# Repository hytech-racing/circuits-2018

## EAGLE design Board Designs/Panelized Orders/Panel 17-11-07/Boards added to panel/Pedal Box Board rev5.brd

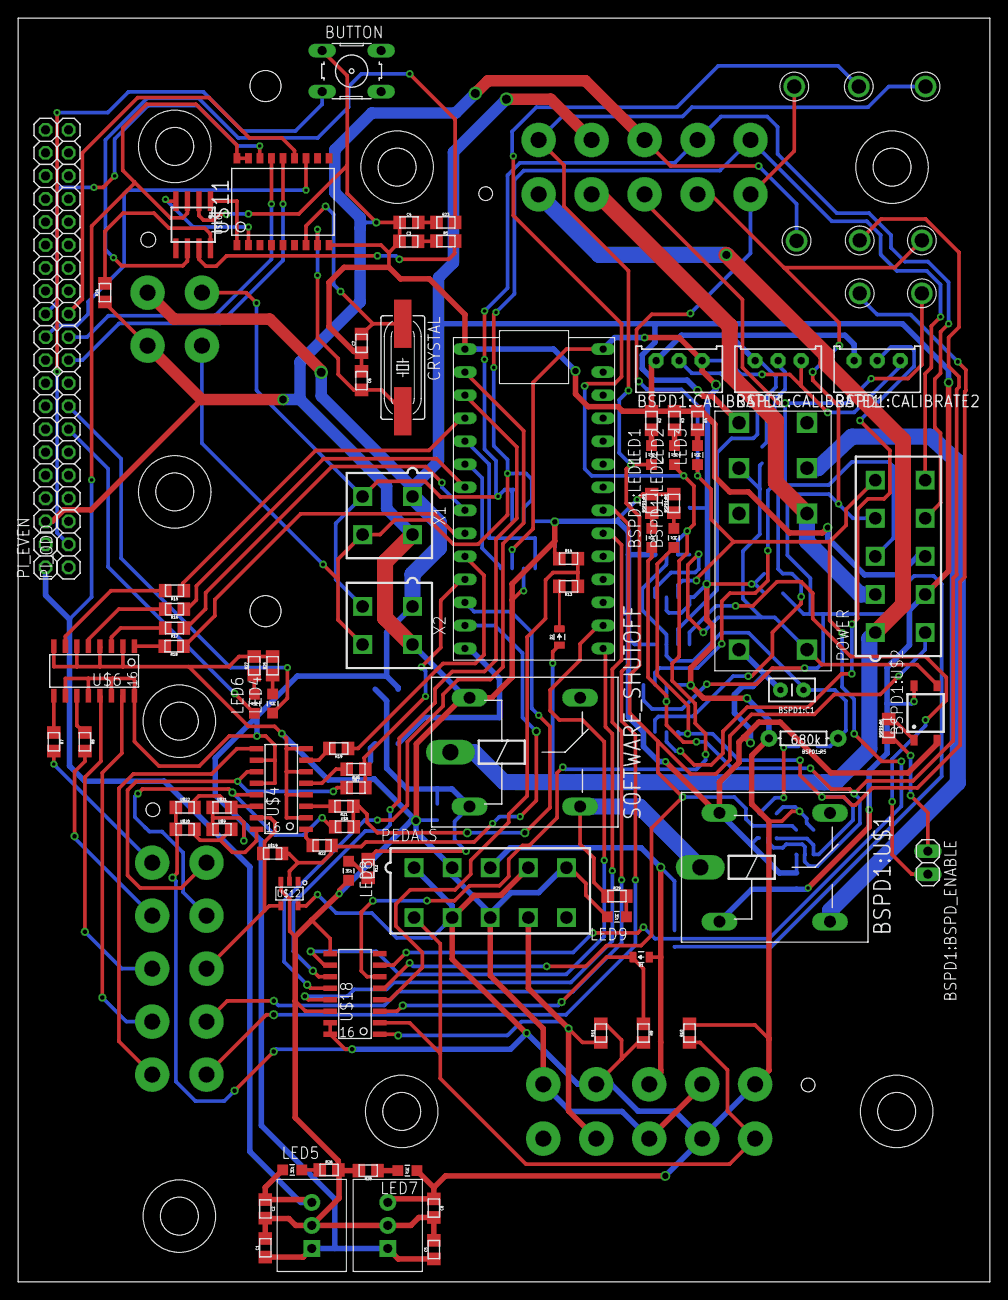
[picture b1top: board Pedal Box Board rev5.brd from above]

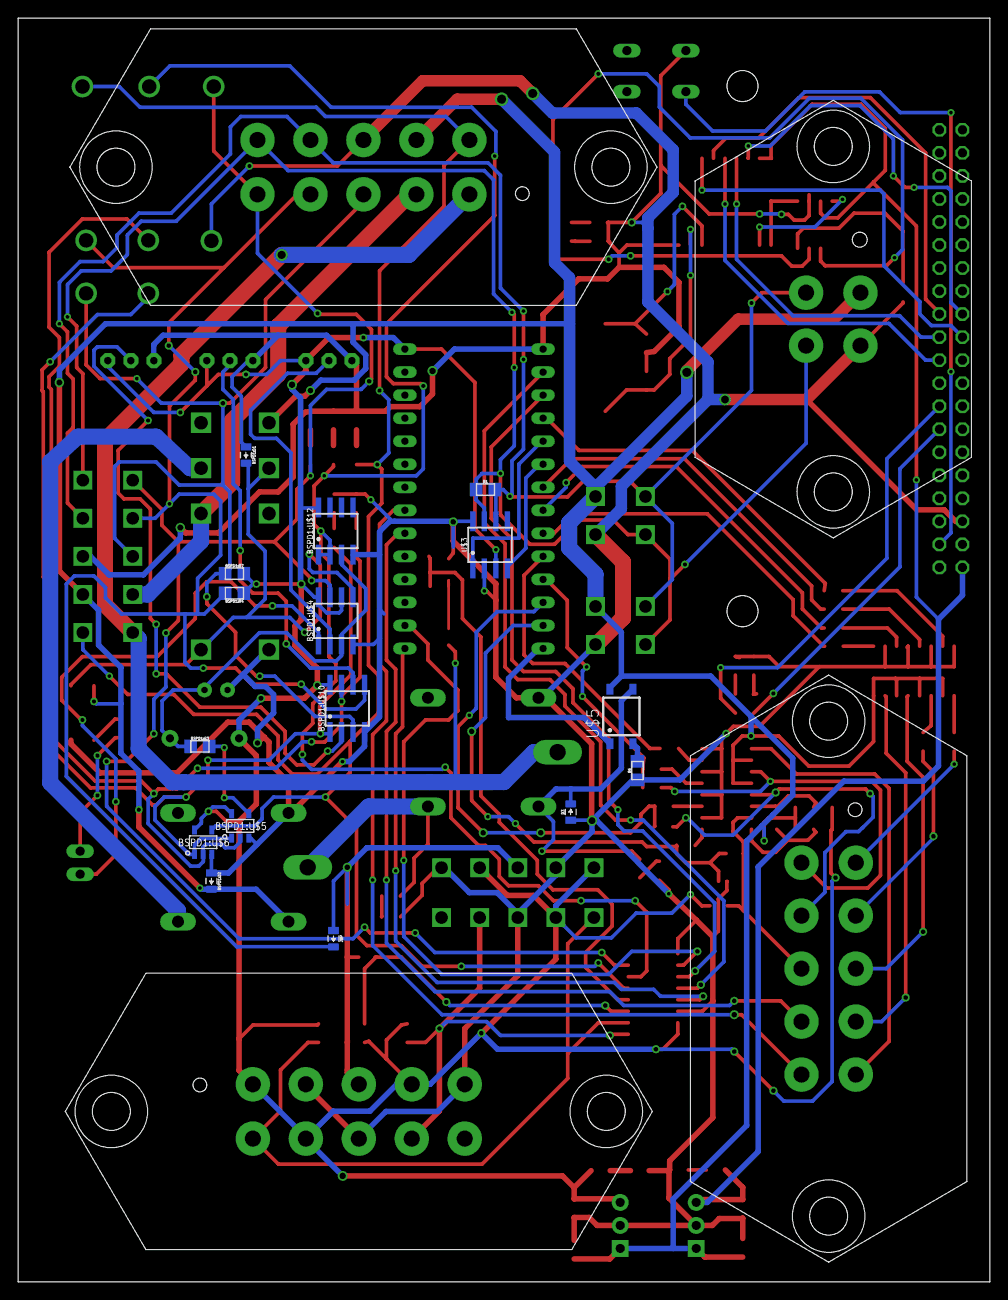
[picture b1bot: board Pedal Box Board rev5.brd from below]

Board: 2 copper layers, 107.2 x 139.4 mm, 113 parts (20 on the bottom side), 99 nets.

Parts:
BSPD1:BSPD_ENABLE: JUMPER; 1X02
BSPD1:C1: .47u; CAP-PTH-SMALLEZ
BSPD1:CALIBRATE1, BSPD1:CALIBRATE2, BSPD1:CALIBRATE3: TRIMPOT_3296
BSPD1:D1, BSPD1:D2: DIODE0805; 0805_D
BSPD1:LED1: RED; LED-805
BSPD1:LED2: YELLOW; LED-805
BSPD1:R3: 330; 0805
BSPD1:R4, BSPD1:R7: 10k; 0805
BSPD1:R5: 680k; AXIAL-0.3EZ
BSPD1:R6: 680; 0805
BSPD1:R8, BSPD1:R9: 270; 0805
BSPD1:U$1: G5LE; ZF112
BSPD1:U$2: CPC1002N; SOP04
BSPD1:U$3: JW2SN-DC12V; JW2SN
BSPD1:U$4, BSPD1:U$10: MCP6542SOIC; SOIC-08
BSPD1:U$5: SN74AHC1G09; SOT-23-5
BSPD1:U$6: SN74LVC1G08; SOT-23-5
BSPD1:U$11, BSPD1:U$13: TEST_POINT
BSPD1:U$12: MCP6002SOIC; SOIC-08
BUTTON: B3F-10XX
C1, C2, C5, C8: 10uF; 0805
C3, C4: 560pF; 0805
C6, C7: 22pF; 0805
CRYSTAL: 16MHz; HC49UP
D1, D2, D3: DIODE0805; 0805_D
IC2, IC3: TO-220
JMP: DIODE0805; 0805_D
LED1, LED6, LED8, LED9: RED; LED-805
LED2: YELLOW; LED-805
LED3, LED4: GREEN; LED-805
LED5, LED7: PURPLE; LED-805
PEDALS: MINIFIT_5566-10
PI_EVEN: 1X20
PI_ODD: 1X20
POWER: MINIFIT_5566-10
R1: 120; 0805
R2, R3, R15, R16, R17, R18, R19, R20, R21, R22, R27: 270; 0805
R4, R25, R26, R28: 200; 0805
R5, R23: 100; 0805
R6: 330; 0805
R7, R8: 0; 0805
R9, R10, R11: 10k; 0805
R12, R29: 1.2K; 0805
R13: 43k; 0805
R14: 12k; 0805
R24: 4.7k; 0805
SOFTWARE_SHUTOFF: G5LE; ZF112
U$1: TEENSY_3.2_SIMPLE
U$2, U$13, U$14, U$15, U$16, U$17: TEST_POINT
U$3, U$10: MCP2551; SOIC-08
U$4, U$6: TLP291-4; SOIC-16
U$5: CPC1002N; SOP04
U$7, U$8, U$9, U$19, U$20, U$21, U$22: JUMPER; 0805
U$11: MCP2515SMD; SOIC-18W
U$12: SN74LV1T34; SOT-23-5
U$18: MCP3208SOIC; SOIC-16
X1, X2: CONNECTOR-4; MINIFIT_5566-4
X3: CONNECTOR-4MX150L_VERTICAL-4; MX150L_VERTICAL-4
X4, X5, X6: CONNECTOR-10MX150L_VERTICAL-10; MX150L_VERTICAL-10

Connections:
+5V: BSPD1:CALIBRATE1.1, BSPD1:CALIBRATE2.1, BSPD1:CALIBRATE3.1, BSPD1:R4.1, BSPD1:R5.P$2, BSPD1:R7.2, BSPD1:U$4.6, BSPD1:U$4.8, BSPD1:U$5.5, BSPD1:U$6.5, BSPD1:U$10.8, BSPD1:U$12.8, C8.1, IC3.3, LED7.A, PEDALS.1, PEDALS.4, PEDALS.7, R9.2, R10.2, R11.2, U$1.VIN, U$3.3, U$12.5, U$18.15, U$18.16, U$20.1, U$22.1, X4.1, X4.4, X4.7
+5V/1: C2.1, IC2.3, LED5.A, PI_EVEN.1, U$10.3, U$11.17, U$11.18
+12V: BSPD1:D2.C, BSPD1:U$1.2, BSPD1:U$2.4, BSPD1:U$3.4, C1.1, C5.1, IC2.1, IC3.1, POWER.7, U$4.10, U$4.12, U$5.4, U$6.10, U$6.12, U$6.14, U$6.16, U$9.1, U$21.1, X1.1, X2.1, X3.1, X5.7
BSPD1:N$1: BSPD1:D1.C, BSPD1:U$2.3, BSPD1:U$3.3, BSPD1:U$3.COIL-, BSPD1:U$4.5
BSPD1:N$2: BSPD1:R3.2, BSPD1:U$5.4
BSPD1:N$3: BSPD1:R6.2, BSPD1:U$2.1
BSPD1:N$4: BSPD1:BSPD_ENABLE.1, BSPD1:R6.1
BSPD1:N$5: BSPD1:CALIBRATE2.2, BSPD1:U$10.2
BSPD1:N$6: BSPD1:CALIBRATE1.2, BSPD1:U$10.6
BSPD1:N$7: BSPD1:CALIBRATE3.2, BSPD1:U$4.2
BSPD1:N$8: BSPD1:BSPD_ENABLE.2, BSPD1:U$4.1
BSPD1:N$13: BSPD1:C1.1, BSPD1:R3.1, BSPD1:R5.P$1, BSPD1:U$4.3, BSPD1:U$12.3
BSPD1:N$14: BSPD1:LED2.C, BSPD1:R8.1
BSPD1:N$15: BSPD1:LED1.C, BSPD1:R9.1
BSPD1:N$16: BSPD1:LED1.A, BSPD1:U$5.2, BSPD1:U$6.2, BSPD1:U$10.7, BSPD1:U$11.P$1
BSPD1:N$17: BSPD1:LED2.A, BSPD1:U$5.1, BSPD1:U$6.1, BSPD1:U$10.1, BSPD1:U$13.P$1
BSPD1:SHUTDOWN_C: BSPD1:U$1.S, BSPD1:U$3.6
BUT: BUTTON.3, PI_ODD.2
CAN-H: R5.2, U$10.7
CAN-L: R23.2, U$10.6
CANH: POWER.10, R1.1, U$3.7, X1.4, X2.4, X3.4, X5.10
CANL: POWER.9, R1.2, U$3.6, X1.3, X2.3, X3.3, X5.9
CS: PI_EVEN.12, U$11.16
DASH_CTRL1: R15.1, U$1.D2
DASH_CTRL2: R16.1, U$1.D5
DASH_CTRL3: R17.1, U$1.D6
DASH_CTRL4: R18.1, U$1.D7(RX3)
DASH_CTRL5: R19.1, U$1.D8(TX3)
DASH_CTRL6: R20.1, U$1.D9(RX2), U$7.2
DASH_CTRL7: R21.1, U$1.D10(TX2), U$8.2
DASH_CTRL8: R22.1, U$1.D11, U$12.2, U$19.2
DASH_CTRL9: U$1.A4, X6.9
DASH_CTRL10: U$1.A5, X6.10
DASH_IO1: R7.2, X6.1
DASH_IO2: R8.2, X6.2
DASH_IO3: U$6.13, X6.3
DASH_IO4: U$6.15, X6.4
DASH_IO5: U$4.9, X6.5
DASH_IO6: U$4.11, U$7.1, X6.6
DASH_IO7: U$4.13, U$8.1, X6.7
DASH_IO8: U$4.15, U$12.4, U$19.1, X6.8
GND: BSPD1:C1.2, BSPD1:CALIBRATE1.3, BSPD1:CALIBRATE2.3, BSPD1:CALIBRATE3.3, BSPD1:D1.A, BSPD1:D2.A, BSPD1:R8.2, BSPD1:R9.2, BSPD1:U$1.1, BSPD1:U$2.2, BSPD1:U$3.COIL+, BSPD1:U$4.4, BSPD1:U$5.3, BSPD1:U$6.3, BSPD1:U$10.4, BSPD1:U$12.4, BUTTON.1, C1.2, C2.2, C3.1, C4.1, C5.2, C6.1, C7.1, C8.2, D3.A, IC2.2, IC3.2, LED8.C, LED9.C, PEDALS.2, PEDALS.5, PEDALS.8, PI_EVEN.3, POWER.8, R2.1, R3.1, R4.1, R6.1, R14.1, R24.1, R25.2, R26.2, R27.2, R28.2, SOFTWARE_SHUTOFF.1, U$1.GND, U$2.P$1, U$3.2, U$3.8, U$4.2, U$4.4, U$4.6, U$4.8, U$6.2, U$6.4, U$6.6, U$6.8, U$10.2, U$11.9, U$12.3, U$18.9, U$18.14, X1.2, X2.2, X3.2, X4.2, X4.5, X4.8, X5.8
INT: PI_EVEN.11, U$11.12
LED1: LED4.A, PI_ODD.8
LED2: LED6.A, PI_ODD.7
MCP3208_CS: U$1.A0, U$18.10
MCP3208_DIN: U$1.D1(TX1), U$18.11
MCP3208_DOUT: U$1.D0(RX1), U$18.12
MCP3208_SCK: U$1.D13, U$18.13
MISO: PI_ODD.11, U$11.15
MOSI: PI_ODD.10, U$11.14
unnamed: R7.1, U$6.9
unnamed: U$1.D4(CANRX), U$3.4
unnamed: R8.1, U$6.11
unnamed: U$4.16, U$9.2, U$20.2
unnamed: U$1.D3(CANTX), U$3.1
unnamed: U$4.14, U$21.2, U$22.2
unnamed: D1.C, R9.1, U$18.3
unnamed: LED8.A, R12.2
unnamed: LED9.A, R29.2
unnamed: D3.C, R12.1, SOFTWARE_SHUTOFF.2, U$5.3
unnamed: D2.C, R13.2
unnamed: LED1.C, R2.2
unnamed: LED2.C, R3.2
unnamed: LED3.C, R4.2
unnamed: R15.2, U$6.7
unnamed: R6.2, U$5.2
unnamed: R16.2, U$6.5
unnamed: R21.2, U$4.3
unnamed: R17.2, U$6.3
unnamed: R18.2, U$6.1
unnamed: R19.2, U$4.7
unnamed: R20.2, U$4.5
unnamed: R22.2, U$4.1
unnamed: U$10.1, U$11.1
unnamed: U$10.4, U$11.2
unnamed: C6.2, CRYSTAL.2, U$11.8
unnamed: R24.2, U$10.8
unnamed: C7.2, CRYSTAL.1, U$11.7
unnamed: C3.2, R5.1
unnamed: C4.2, R23.1
unnamed: LED4.C, R25.1
unnamed: LED5.C, R26.1
unnamed: LED6.C, R27.1
unnamed: LED7.C, R28.1
RAW_ACCEL1: PEDALS.9, R11.1, U$18.1, X4.9
RAW_ACCEL2: PEDALS.6, R10.1, U$18.2, X4.6
RAW_BRAKE: D1.A, JMP.A, PEDALS.3, X4.3
READ_CHARGE: BSPD1:U$12.1, BSPD1:U$12.2, LED2.A, U$16.P$1, U$18.6
READ_FAULT: BSPD1:U$4.7, LED3.A, POWER.5, U$15.P$1, U$18.7, X5.5
READ_SWITCH: BSPD1:U$6.4, LED1.A, POWER.6, U$17.P$1, U$18.5, X5.6
READ_UPSTREAM_SHUTDOWN: R13.1, R14.2, U$18.4
SCK: PI_ODD.12, U$11.13
SHUTDOWN_A: D2.A, POWER.1, SOFTWARE_SHUTOFF.P, X5.1
SHUTDOWN_B: BSPD1:U$1.P, R29.1, SOFTWARE_SHUTOFF.S
SHUTDOWN_D: BSPD1:U$3.7, POWER.2, X5.2
SHUTDOWN_RELAY_CTRL: U$1.D12, U$5.1
SIGNAL_BRAKE: BSPD1:R4.2, BSPD1:U$10.5, JMP.C, POWER.4, U$13.P$1, X5.4
SIGNAL_CURRENT: BSPD1:R7.1, BSPD1:U$10.3, POWER.3, U$14.P$1, X5.3

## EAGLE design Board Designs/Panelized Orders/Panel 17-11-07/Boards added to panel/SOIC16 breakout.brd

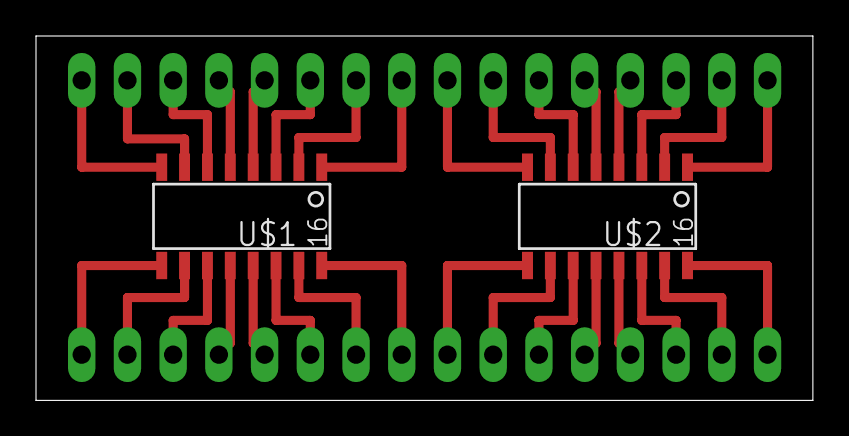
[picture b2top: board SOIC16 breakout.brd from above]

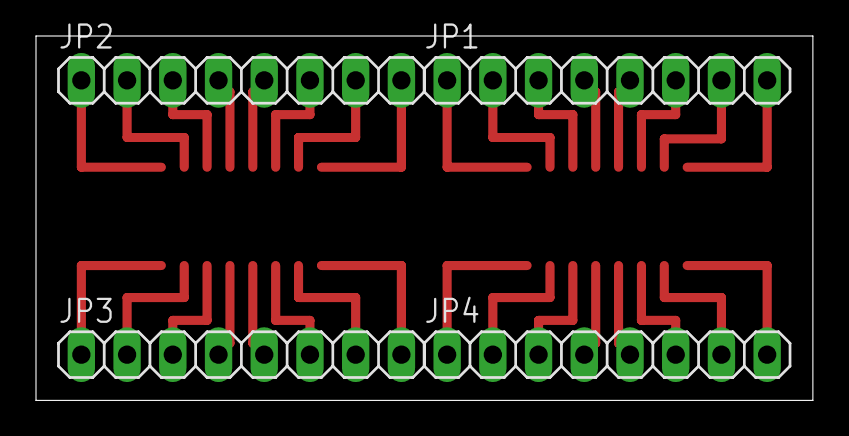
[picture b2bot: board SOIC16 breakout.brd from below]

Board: 2 copper layers, 43.2 x 20.2 mm, 6 parts (4 on the bottom side), 32 nets.

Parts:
JP1, JP2, JP3, JP4: 1X08
U$1, U$2: SOIC16; SOIC-16

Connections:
unnamed: JP1.1, U$1.1
unnamed: JP1.2, U$1.2
unnamed: JP1.3, U$1.3
unnamed: JP1.4, U$1.4
unnamed: JP1.5, U$1.5
unnamed: JP1.6, U$1.6
unnamed: JP1.7, U$1.7
unnamed: JP1.8, U$1.8
unnamed: JP2.1, U$2.1
unnamed: JP2.2, U$2.2
unnamed: JP2.3, U$2.3
unnamed: JP2.4, U$2.4
unnamed: JP2.5, U$2.5
unnamed: JP2.6, U$2.6
unnamed: JP2.7, U$2.7
unnamed: JP2.8, U$2.8
unnamed: JP3.1, U$2.16
unnamed: JP3.2, U$2.15
unnamed: JP3.3, U$2.14
unnamed: JP3.4, U$2.13
unnamed: JP3.5, U$2.12
unnamed: JP3.6, U$2.11
unnamed: JP3.7, U$2.10
unnamed: JP3.8, U$2.9
unnamed: JP4.1, U$1.16
unnamed: JP4.2, U$1.15
unnamed: JP4.3, U$1.14
unnamed: JP4.4, U$1.13
unnamed: JP4.5, U$1.12
unnamed: JP4.6, U$1.11
unnamed: JP4.7, U$1.10
unnamed: JP4.8, U$1.9

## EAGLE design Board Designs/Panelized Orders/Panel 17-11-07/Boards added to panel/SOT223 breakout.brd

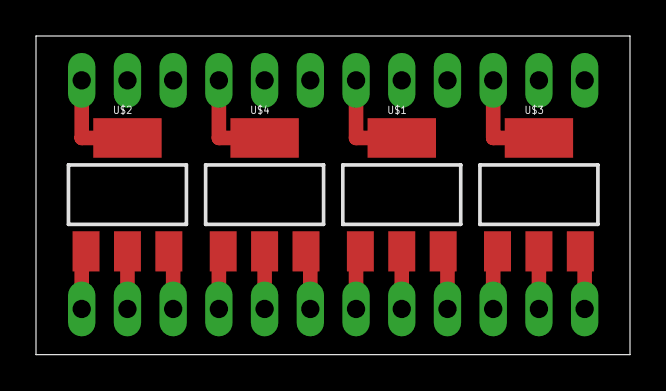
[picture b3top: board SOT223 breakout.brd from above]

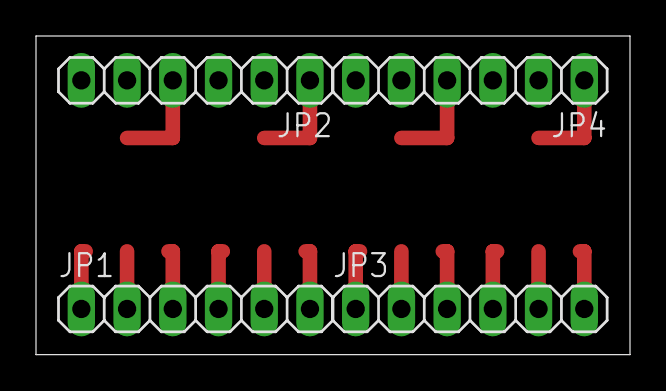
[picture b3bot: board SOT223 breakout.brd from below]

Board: 2 copper layers, 33.0 x 17.7 mm, 8 parts (4 on the bottom side), 16 nets.

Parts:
JP1, JP2, JP3, JP4: 1X06
U$1, U$2, U$3, U$4: SOT223

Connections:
unnamed: JP2.1, U$1.4
unnamed: JP1.6, U$1.1
unnamed: JP1.5, U$1.2
unnamed: JP1.4, U$1.3
unnamed: JP1.3, U$3.1
unnamed: JP1.2, U$3.2
unnamed: JP1.1, U$3.3
unnamed: JP2.4, U$3.4
unnamed: JP4.1, U$2.4
unnamed: JP4.4, U$4.4
unnamed: JP3.6, U$2.1
unnamed: JP3.5, U$2.2
unnamed: JP3.4, U$2.3
unnamed: JP3.3, U$4.1
unnamed: JP3.2, U$4.2
unnamed: JP3.1, U$4.3

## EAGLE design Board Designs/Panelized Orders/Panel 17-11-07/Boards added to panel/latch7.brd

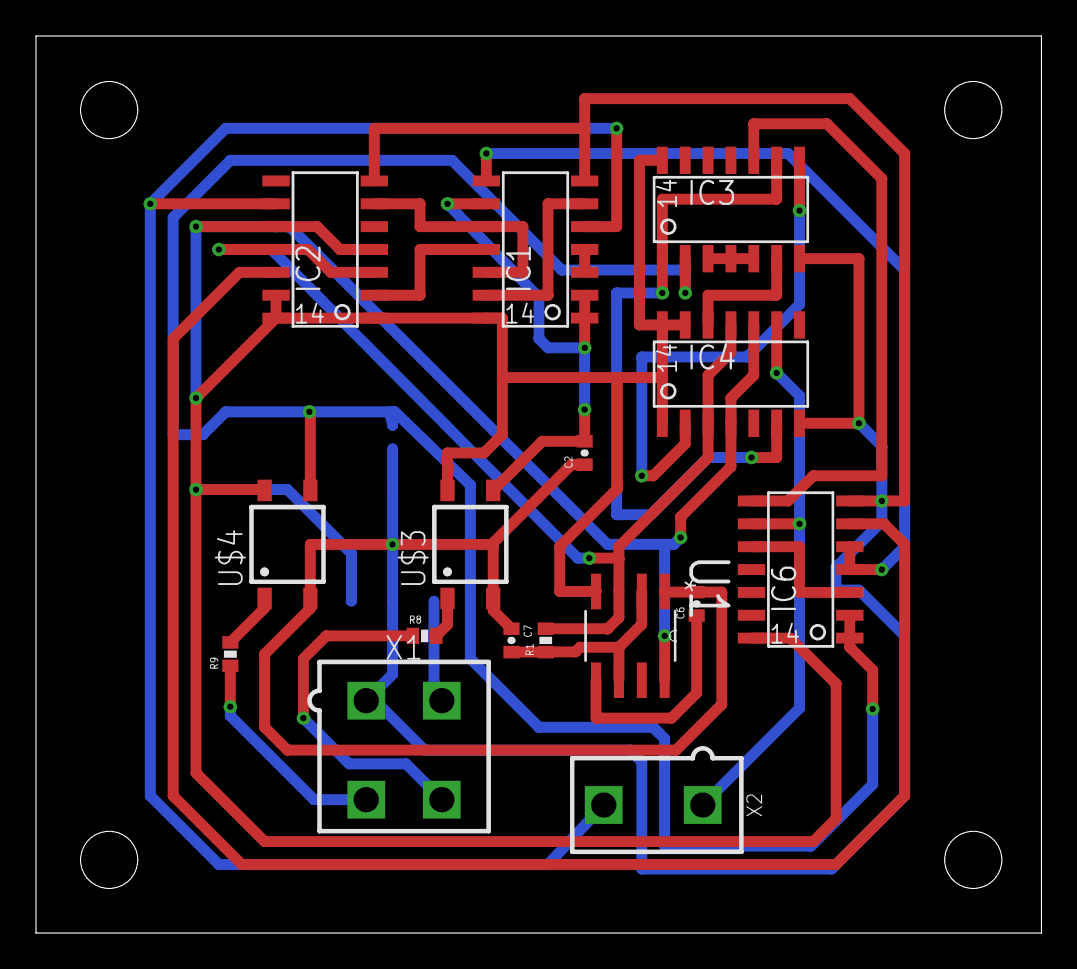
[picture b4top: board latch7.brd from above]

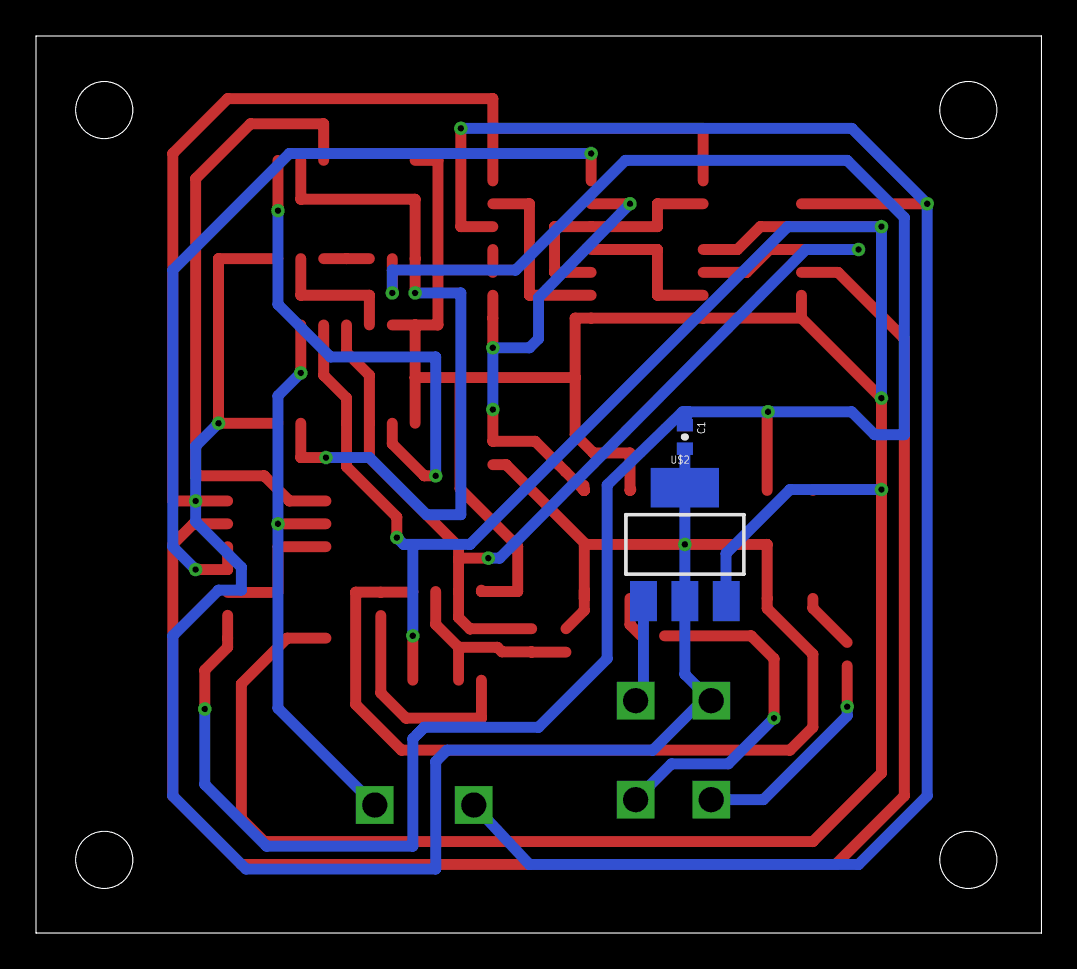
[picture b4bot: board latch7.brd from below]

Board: 2 copper layers, 55.9 x 49.8 mm, 18 parts (2 on the bottom side), 26 nets.

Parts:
C1, C2: 0402-CAP
C6, C7: 10nF; 0402-CAP
IC1, IC3, IC6: SN74AHC00D; SOIC-14
IC2, IC4: SN74AHC74D; SOIC-14
R1: 100kΩ; 0402-RES
R8, R9: 680Ω; 0402-RES
U1: SA555D; SOIC127P600X175-8N
U$2: SOT223
U$3, U$4: CPC1002N; SOP04
X1: CONNECTOR-4; MINIFIT_5566-4
X2: CONNECTOR-2; MINIFIT_5566-2

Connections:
12V: U$2.1, X1.2
+5V: IC1.14, IC2.1, IC2.4, IC2.10, IC2.13, IC2.14, IC3.14, IC4.1, IC4.4, IC4.10, IC4.13, IC4.14, IC6.14, U1.4, U1.8, U$2.3, U$3.4, U$4.4
BMS_5V: C1.1, IC3.2, IC6.1, IC6.2, U$4.3
BMS_IN: R9.2, U$4.1
BMS_OUT: IC4.9, IC6.9, X2.1
GND: C1.2, C2.1, C6.2, C7.1, IC1.7, IC2.7, IC3.7, IC4.7, IC6.7, U1.1, U$2.2, U$2.4, U$3.2, U$4.2, X1.1
IMD_5V: C2.2, IC1.1, IC1.2, IC1.9, U$3.3
IMD_IN: R8.2, U$3.1
IMD_OUT: IC1.5, IC2.9, X2.2
unnamed: IC2.3, IC2.11, IC4.3, IC4.11, R1.2, U1.3
unnamed: IC1.3, IC1.4
unnamed: C7.2, R1.1, U1.2, U1.6
unnamed: IC1.6, IC1.13
unnamed: IC1.10, IC1.12, IC2.6
unnamed: IC1.11, IC2.2
unnamed: IC2.12, IC6.6
unnamed: C6.1, U1.5
unnamed: IC3.6, IC4.12
unnamed: IC1.8, IC6.4, IC6.5
unnamed: IC6.3, IC6.10
unnamed: IC3.10, IC6.8
unnamed: IC3.1, IC3.9, IC4.6
unnamed: IC3.8, IC4.2
unnamed: IC3.3, IC3.4, IC3.5
unnamed: R8.1, X1.4
unnamed: R9.1, X1.3

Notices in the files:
parts and their libraries:
SparkFun-FreqCtrl: Licensing: Creative Commons ShareAlike 4.0 International - https://creativecommons.org/licenses/by-sa/4.0
